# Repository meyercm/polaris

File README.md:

# Upload Command

`platformio run --target upload` Build project and upload firmware to the all devices specified in Project Configuration File platformio.ini

## Current issues:

- Missing trace on board in upper right corner between I2C pull-up resistors
- Feather pin 9 is not capable of PWM, despite documentation.  can't use motor controllers
  as intended.

## Links

- [Ardunio example I2C](https://www.arduino.cc/en/Tutorial/DigitalPotentiometer)
- [Compass Datasheet](http://cache.freescale.com/files/sensors/doc/data_sheet/MAG3110.pdf)
- [Compass Appnote](http://www.nxp.com/assets/documents/data/en/application-notes/AN4984.pdf)

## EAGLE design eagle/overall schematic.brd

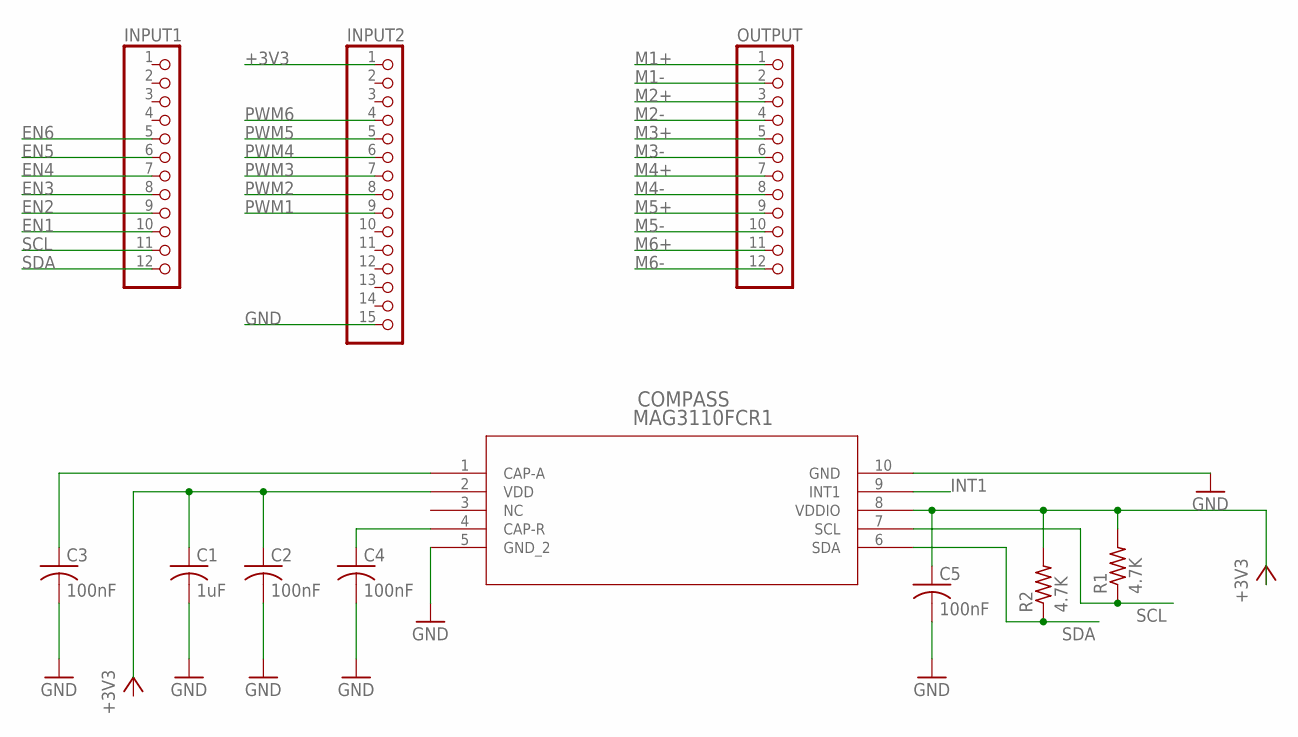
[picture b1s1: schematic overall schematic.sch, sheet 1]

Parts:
C1: 1uF; C0603
C2, C3, C4, C5: 100nF; C0603
COMPASS: MAG3110FCR1; DFN10
INPUT1: PINHD-1X12-CB; 1X12-CB
INPUT2: PINHD-1X15-CB; 1X15-CB
OUTPUT: PINHD-1X12-CB; 1X12-CB
R1, R2: 4.7K; R0603

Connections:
+3V3: C5.1, COMPASS.8 (VDDIO), INPUT2.1, R1.2, R2.2; also elsewhere on the board
CAP-A: C3.1, COMPASS.1 (CAP-A)
CAP-R: C4.1, COMPASS.4 (CAP-R)
EN1: INPUT1.10; also elsewhere on the board
EN2: INPUT1.9; also elsewhere on the board
EN3: INPUT1.8; also elsewhere on the board
EN4: INPUT1.7; also elsewhere on the board
EN5: INPUT1.6; also elsewhere on the board
EN6: INPUT1.5; also elsewhere on the board
GND: C1.2, C2.2, C3.2, C4.2, C5.2, COMPASS.5 (GND_2), COMPASS.10 (GND), INPUT2.15; also elsewhere on the board
INT1: COMPASS.9 (INT1)
M1+: OUTPUT.1; also elsewhere on the board
M1-: OUTPUT.2; also elsewhere on the board
M2+: OUTPUT.3; also elsewhere on the board
M2-: OUTPUT.4; also elsewhere on the board
M3+: OUTPUT.5; also elsewhere on the board
M3-: OUTPUT.6; also elsewhere on the board
M4+: OUTPUT.7; also elsewhere on the board
M4-: OUTPUT.8; also elsewhere on the board
M5+: OUTPUT.9; also elsewhere on the board
M5-: OUTPUT.10; also elsewhere on the board
M6+: OUTPUT.11; also elsewhere on the board
M6-: OUTPUT.12; also elsewhere on the board
unnamed: C1.1, C2.1, COMPASS.2 (VDD)
PWM1: INPUT2.9; also elsewhere on the board
PWM2: INPUT2.8; also elsewhere on the board
PWM3: INPUT2.7; also elsewhere on the board
PWM4: INPUT2.6; also elsewhere on the board
PWM5: INPUT2.5; also elsewhere on the board
PWM6: INPUT2.4; also elsewhere on the board
SCL: COMPASS.7 (SCL), INPUT1.11, R1.1
SDA: COMPASS.6 (SDA), INPUT1.12, R2.1

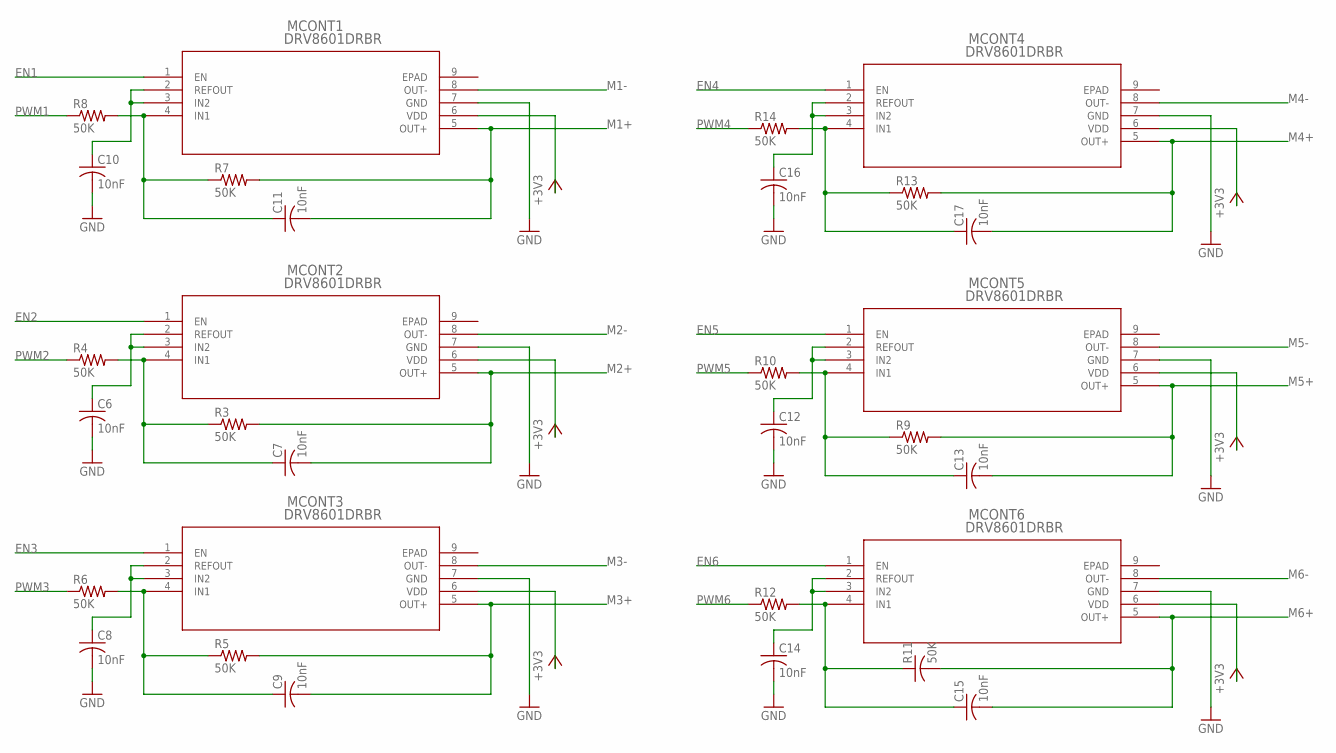
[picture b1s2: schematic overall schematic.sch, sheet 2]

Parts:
C6, C7, C8, C9, C10, C11, C12, C13, C14, C15, C16, C17: 10nF; C0603
MCONT1, MCONT2, MCONT3, MCONT4, MCONT5, MCONT6: DRV8601DRBR; DRB8_1P75X1P5
R3, R4, R5, R6, R7, R8, R9, R10, R12, R13, R14: 50K; R0603
R11: 50K; C0603

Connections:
+3V3: MCONT1.6 (VDD), MCONT2.6 (VDD), MCONT3.6 (VDD), MCONT4.6 (VDD), MCONT5.6 (VDD), MCONT6.6 (VDD); also elsewhere on the board
EN1: MCONT1.1 (EN); also elsewhere on the board
EN2: MCONT2.1 (EN); also elsewhere on the board
EN3: MCONT3.1 (EN); also elsewhere on the board
EN4: MCONT4.1 (EN); also elsewhere on the board
EN5: MCONT5.1 (EN); also elsewhere on the board
EN6: MCONT6.1 (EN); also elsewhere on the board
FB1: C11.1, MCONT1.4 (IN1), R7.1, R8.2
FB2: C7.1, MCONT2.4 (IN1), R3.1, R4.2
FB3: C9.1, MCONT3.4 (IN1), R5.1, R6.2
FB4: C17.1, MCONT4.4 (IN1), R13.1, R14.2
FB5: C13.1, MCONT5.4 (IN1), R9.1, R10.2
FB6: C15.1, MCONT6.4 (IN1), R11.1, R12.2
FBA1: C10.1, MCONT1.2 (REFOUT), MCONT1.3 (IN2)
FBA2: C6.1, MCONT2.2 (REFOUT), MCONT2.3 (IN2)
FBA3: C8.1, MCONT3.2 (REFOUT), MCONT3.3 (IN2)
FBA4: C16.1, MCONT4.2 (REFOUT), MCONT4.3 (IN2)
FBA5: C12.1, MCONT5.2 (REFOUT), MCONT5.3 (IN2)
FBA6: C14.1, MCONT6.2 (REFOUT), MCONT6.3 (IN2)
GND: C6.2, C8.2, C10.2, C12.2, C14.2, C16.2, MCONT1.7 (GND), MCONT2.7 (GND), MCONT3.7 (GND), MCONT4.7 (GND), MCONT5.7 (GND), MCONT6.7 (GND); also elsewhere on the board
M1+: C11.2, MCONT1.5 (OUT+), R7.2; also elsewhere on the board
M1-: MCONT1.8 (OUT-); also elsewhere on the board
M2+: C7.2, MCONT2.5 (OUT+), R3.2; also elsewhere on the board
M2-: MCONT2.8 (OUT-); also elsewhere on the board
M3+: C9.2, MCONT3.5 (OUT+), R5.2; also elsewhere on the board
M3-: MCONT3.8 (OUT-); also elsewhere on the board
M4+: C17.2, MCONT4.5 (OUT+), R13.2; also elsewhere on the board
M4-: MCONT4.8 (OUT-); also elsewhere on the board
M5+: C13.2, MCONT5.5 (OUT+), R9.2; also elsewhere on the board
M5-: MCONT5.8 (OUT-); also elsewhere on the board
M6+: C15.2, MCONT6.5 (OUT+), R11.2; also elsewhere on the board
M6-: MCONT6.8 (OUT-); also elsewhere on the board
PWM1: R8.1; also elsewhere on the board
PWM2: R4.1; also elsewhere on the board
PWM3: R6.1; also elsewhere on the board
PWM4: R14.1; also elsewhere on the board
PWM5: R10.1; also elsewhere on the board
PWM6: R12.1; also elsewhere on the board

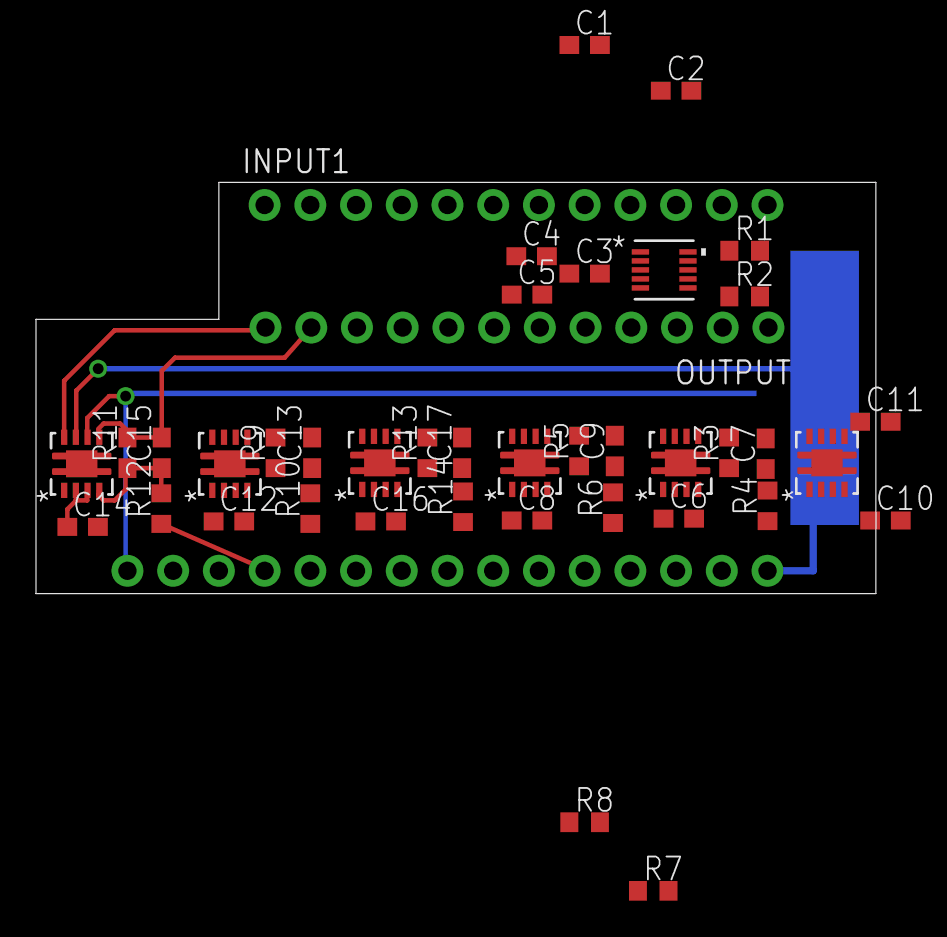
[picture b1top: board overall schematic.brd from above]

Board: 2 copper layers, 46.7 x 22.9 mm, 41 parts (0 on the bottom side), 43 nets.

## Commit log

2016-12-06 development code for prototyping components
2016-12-06 add eagle design files
2016-12-24 motor controller 1 test
2016-12-24 compass section ready
2016-12-24 not working, not sure why
2016-12-24 working again
2016-12-24 removing debug statements
2016-12-24 just stopped working... dunno why
2016-12-24 needed to be re-plugged. fixed normalization math
2016-12-25 functional, yet hacky motor control
2016-12-25 removed unused lib
2016-12-25 added transforms
2016-12-25 hacking out troubling parts
2016-12-26 single motor, transform on
2016-12-27 only a single ring of motors, seems to work decently
2016-12-28 all 6 motors in a ring
2016-12-28 attempt for omnidirectional awareness

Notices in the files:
parts and their libraries:
COPYRIGHT: Copyright C 2015 Accelerated Designs. All rights reserved
